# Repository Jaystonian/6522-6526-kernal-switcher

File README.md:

# 6522-6526-kernal-switcher
Adaptation of Sven Petersen's Keyboard Kernal Switch for MOS6522 or MOS6526 (VIC-20, C64, C128)

An ATMEGA328P microcontroller connected to the keyboard wires to listen for changes to keypresses 
of most of the top row of the keyboard. Hold down a number key and press RESTORE, (VIC-20 has 
limited compatibility) and three output bits (A B & C) for system control can be toggled by code.
The LED and bottom jumper can be wired directly (behind the resistor from the LED pin for example) 
and reprogrammed to use those as two extra output bits. Inputs can be reprogrammed to include + 
and - for example and then increase/decrease the selected output to control multiple EPROMs or 
devices for different reboot modes.  Memory controller modes, other ROMs, better control over more 
function roms in a C128 with more KERNAL ROMs (2 and 4 or 4 and 2 work well together with just ABC)
or memory maps etc.  With 5 you can dedicate 2 and 3 (giving 4 and 8 selections) instead of sharing 
lines as demonstrated in the C128 installation.

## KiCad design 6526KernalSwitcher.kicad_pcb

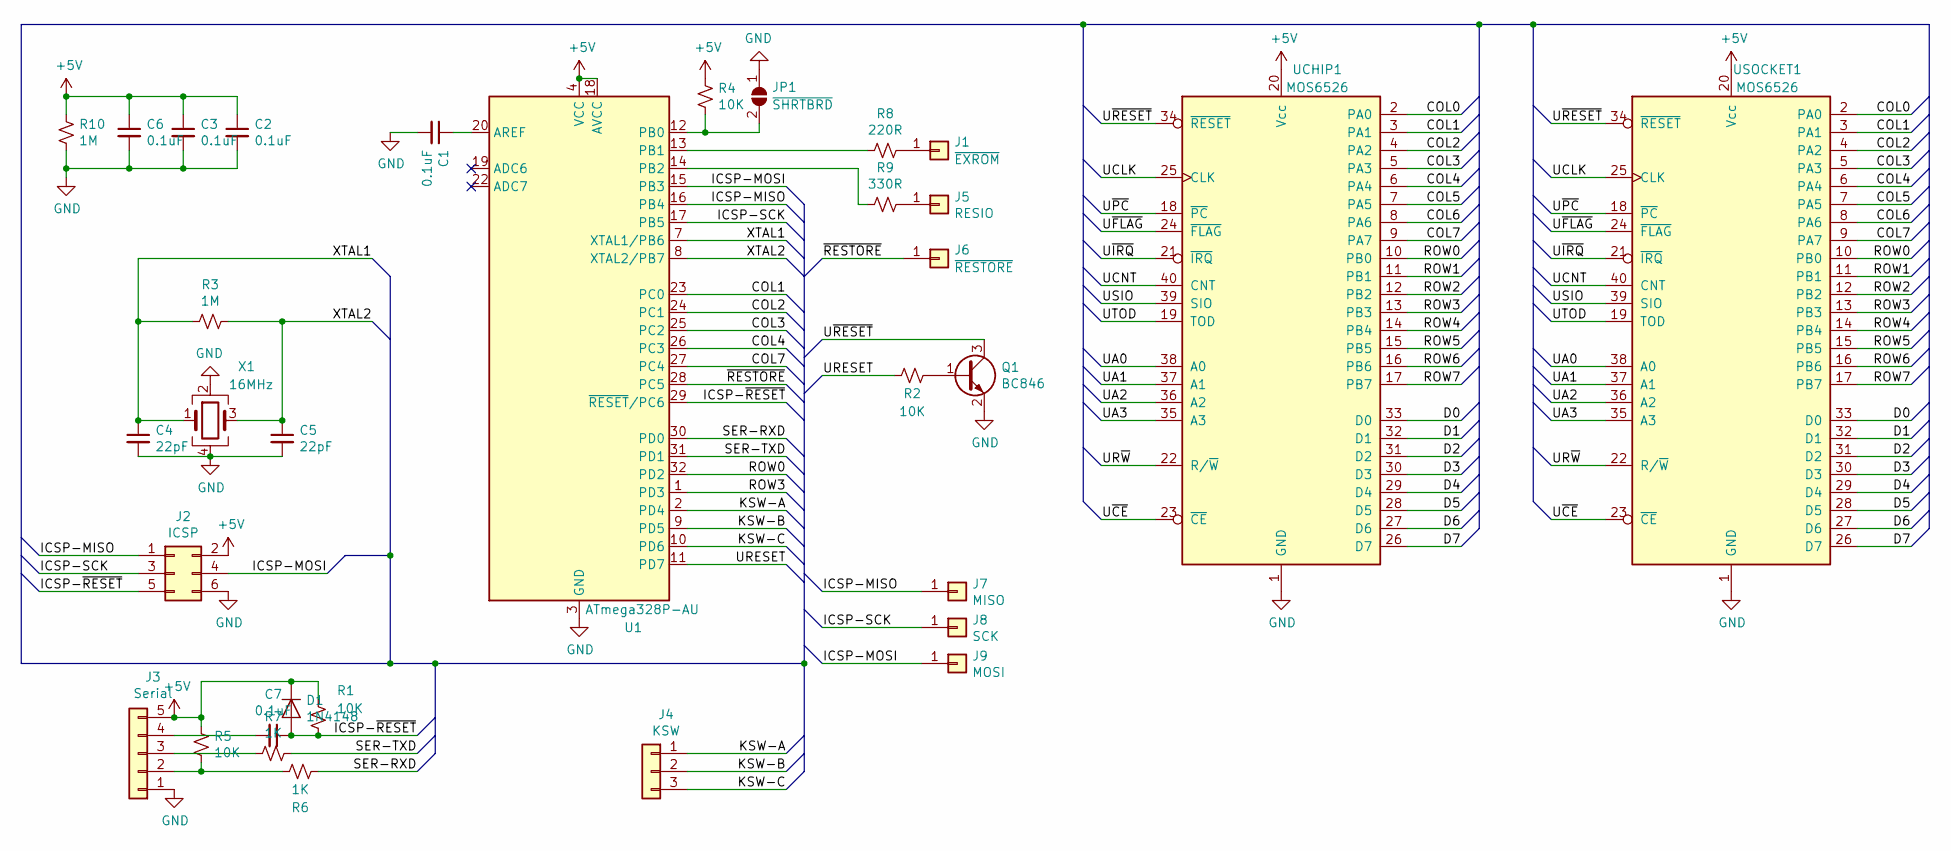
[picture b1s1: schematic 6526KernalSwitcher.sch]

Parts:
C1, C2, C3, C6, C7: 0.1uF; C_0805_2012Metric_Pad1.15x1.40mm_HandSolder
C4, C5: 22pF; C_0805_2012Metric_Pad1.15x1.40mm_HandSolder
D1: 1N4148; D_MiniMELF
J1: ~EXROM; PinHeader_1x01_P2.54mm_Vertical
J2: ICSP; PinHeader_2x03_P2.54mm_Vertical
J3: Serial; PinHeader_1x05_P2.54mm_Vertical
J4: KSW; PinHeader_1x03_P2.54mm_Vertical
J5: RESIO; PinHeader_1x01_P2.54mm_Vertical
J6: ~RESTORE; PinHeader_1x01_P2.54mm_Vertical
J7: MISO; SolderPad
J8: SCK; SolderPad
J9: MOSI; SolderPad
JP1: ~SHRTBRD; SolderJumper-2_P1.3mm_Open_RoundedPad1.0x1.5mm
Q1: BC846; SOT-23
R1, R2, R4, R5: 10K; R_0805_2012Metric_Pad1.15x1.40mm_HandSolder
R3, R10: 1M; R_0805_2012Metric_Pad1.15x1.40mm_HandSolder
R6, R7: 1K; R_0805_2012Metric_Pad1.15x1.40mm_HandSolder
R8: 220R; R_0805_2012Metric_Pad1.15x1.40mm_HandSolder
R9: 330R; R_0805_2012Metric_Pad1.15x1.40mm_HandSolder
U1: ATmega328P-AU; TQFP-32_7x7mm_P0.8mm
UCHIP1: MOS6526; DIP-40_W15.24mm
USOCKET1: MOS6526; DIP-40_W15.24mm
X1: 16MHz; Crystal_SMD_2016-4Pin_2.0x1.6mm

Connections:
+5V: C2.1, C3.1, C6.1, D1.1 (K), J2.2, J3.5, R1.1, R4.1, R5.1, R10.1, U1.4 (VCC), U1.6 (VCC), U1.18 (AVCC), UCHIP1.20 (Vcc), USOCKET1.20 (Vcc)
/COL0: UCHIP1.2 (PA0), USOCKET1.2 (PA0)
/COL1: U1.23 (PC0), UCHIP1.3 (PA1), USOCKET1.3 (PA1)
/COL2: U1.24 (PC1), UCHIP1.4 (PA2), USOCKET1.4 (PA2)
/COL3: U1.25 (PC2), UCHIP1.5 (PA3), USOCKET1.5 (PA3)
/COL4: U1.26 (PC3), UCHIP1.6 (PA4), USOCKET1.6 (PA4)
/COL5: UCHIP1.7 (PA5), USOCKET1.7 (PA5)
/COL6: UCHIP1.8 (PA6), USOCKET1.8 (PA6)
/COL7: U1.27 (PC4), UCHIP1.9 (PA7), USOCKET1.9 (PA7)
/D0: UCHIP1.33 (D0), USOCKET1.33 (D0)
/D1: UCHIP1.32 (D1), USOCKET1.32 (D1)
/D2: UCHIP1.31 (D2), USOCKET1.31 (D2)
/D3: UCHIP1.30 (D3), USOCKET1.30 (D3)
/D4: UCHIP1.29 (D4), USOCKET1.29 (D4)
/D5: UCHIP1.28 (D5), USOCKET1.28 (D5)
/D6: UCHIP1.27 (D6), USOCKET1.27 (D6)
/D7: UCHIP1.26 (D7), USOCKET1.26 (D7)
/ICSP-MISO: J2.1, J7.1, U1.16 (PB4)
/ICSP-MOSI: J2.4, J9.1, U1.15 (PB3)
/ICSP-SCK: J2.3, J8.1, U1.17 (PB5)
/ICSP-~RESET: C7.1, D1.2 (A), J2.5, R1.2, U1.29 (~RESET~/PC6)
/KSW-A: J4.1, U1.2 (PD4)
/KSW-B: J4.2, U1.9 (PD5)
/KSW-C: J4.3, U1.10 (PD6)
/ROW0: U1.32 (PD2), UCHIP1.10 (PB0), USOCKET1.10 (PB0)
/ROW1: UCHIP1.11 (PB1), USOCKET1.11 (PB1)
/ROW2: UCHIP1.12 (PB2), USOCKET1.12 (PB2)
/ROW3: U1.1 (PD3), UCHIP1.13 (PB3), USOCKET1.13 (PB3)
/ROW4: UCHIP1.14 (PB4), USOCKET1.14 (PB4)
/ROW5: UCHIP1.15 (PB5), USOCKET1.15 (PB5)
/ROW6: UCHIP1.16 (PB6), USOCKET1.16 (PB6)
/ROW7: UCHIP1.17 (PB7), USOCKET1.17 (PB7)
/SER-RXD: R6.1, U1.30 (PD0)
/SER-TXD: R7.1, U1.31 (PD1)
/UA0: UCHIP1.38 (A0), USOCKET1.38 (A0)
/UA1: UCHIP1.37 (A1), USOCKET1.37 (A1)
/UA2: UCHIP1.36 (A2), USOCKET1.36 (A2)
/UA3: UCHIP1.35 (A3), USOCKET1.35 (A3)
/UCLK: UCHIP1.25 (CLK), USOCKET1.25 (CLK)
/UCNT: UCHIP1.40 (CNT), USOCKET1.40 (CNT)
/URESET: R2.2, U1.11 (PD7)
/UR~W: UCHIP1.22 (R/~W~), USOCKET1.22 (R/~W~)
/USIO: UCHIP1.39 (SIO), USOCKET1.39 (SIO)
/UTOD: UCHIP1.19 (TOD), USOCKET1.19 (TOD)
/U~CE: UCHIP1.23 (~CE~), USOCKET1.23 (~CE~)
/U~FLAG: UCHIP1.24 (~FLAG~), USOCKET1.24 (~FLAG~)
/U~IRQ: UCHIP1.21 (~IRQ~), USOCKET1.21 (~IRQ~)
/U~PC: UCHIP1.18 (~PC~), USOCKET1.18 (~PC~)
/U~RESET: Q1.3 (C), UCHIP1.34 (~RESET~), USOCKET1.34 (~RESET~)
/XTAL1: C4.1, R3.2, U1.7 (XTAL1/PB6), X1.1
/XTAL2: C5.1, R3.1, U1.8 (XTAL2/PB7), X1.3
/~RESTORE: J6.1, U1.28 (PC5)
GND: C1.2, C2.2, C3.2, C4.2, C5.2, C6.2, J2.6, J3.1, JP1.1 (A), Q1.2 (E), R10.2, U1.3 (GND), U1.5 (GND), U1.21 (GND), UCHIP1.1 (GND), USOCKET1.1 (GND), X1.2, X1.4
unnamed: C1.1, U1.20 (AREF)
unnamed: C7.2, J3.4
unnamed: J1.1, R8.1
unnamed: J3.2, R5.2, R6.2
unnamed: J3.3, R7.2
unnamed: J5.1, R9.1
unnamed: JP1.2 (B), R4.2, U1.12 (PB0)
unnamed: Q1.1 (B), R2.1
unnamed: R8.2, U1.13 (PB1)
unnamed: R9.2, U1.14 (PB2)

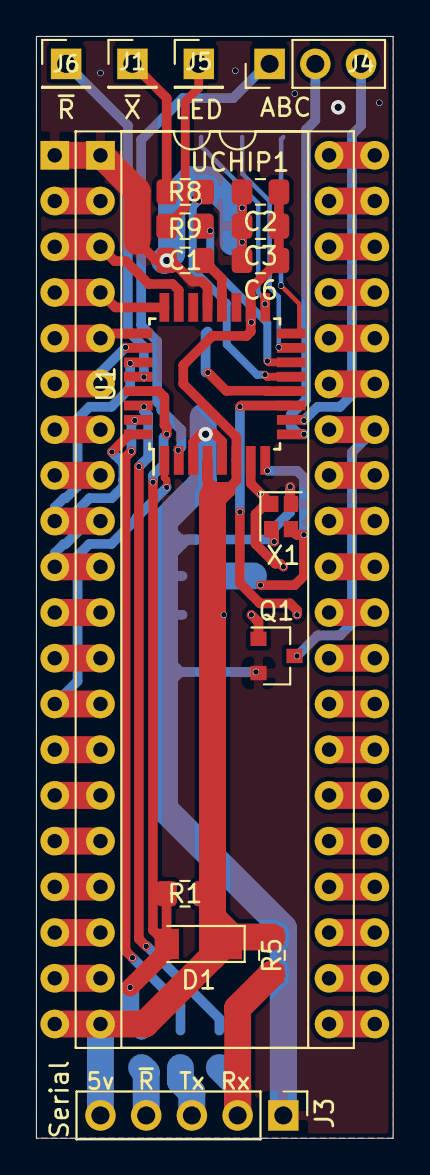
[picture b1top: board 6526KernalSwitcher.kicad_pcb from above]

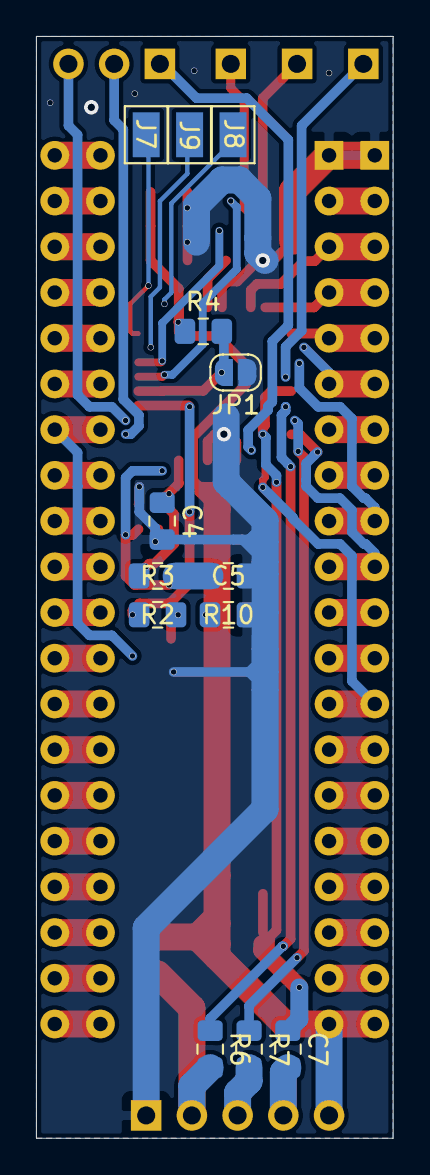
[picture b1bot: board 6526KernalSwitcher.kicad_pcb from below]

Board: 2 copper layers, 19.8 x 61.2 mm, 32 parts (13 on the bottom side), 63 nets.

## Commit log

2020-10-22 Add files via upload
    Update on VIC
